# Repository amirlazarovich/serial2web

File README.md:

# Serial to web
Sample code for AVR serial, web server and a web socket

Thanks to [Tomer Weller](https://github.com/tomerweller/serial-to-socketio)!

### Install
```javascript
sudo npm install
```

### Usage
```javascript
node app [options]

options:
-h,--help			 print usage
-p, --port			 set serial port [default: tty.usb*]
-b, --baudrate		 set baudrate [default: 9600]
-w, --webport		 set web port [default: 8000]
```

### Example
```javascript 
node app
```

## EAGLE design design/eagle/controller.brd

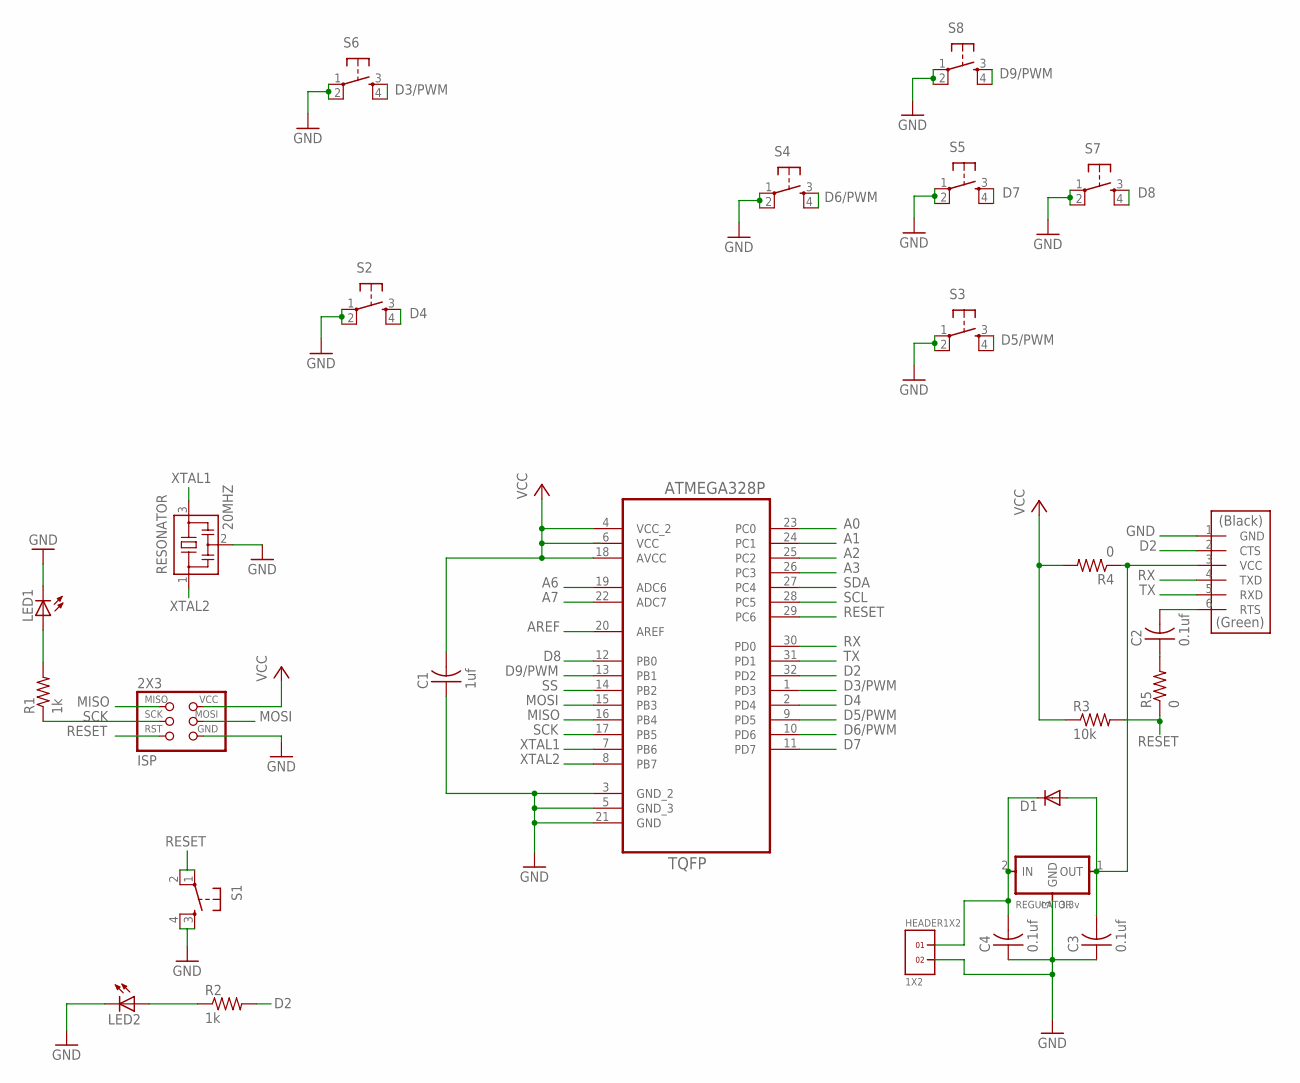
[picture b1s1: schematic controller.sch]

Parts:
2X3: ISP; 2X03SMD
C1: 1uf; C1206
C2, C3, C4: 0.1uf; C1206
D1: DIODESOD123; SOD123
FTDI: FTDI-SMD-HEADER; 1X06SMD
HEADER1X2: 1X2
LED1, LED2: LED_E; LED_1206
R1, R2: 1k; R1206
R3: 10k; R1206
R4, R5: 0; R1206
REGULATOR: 3.3v; SOT23
RESONATOR: 20MHZ; EFOBM
S1, S2, S3, S4, S5, S6, S7, S8: 6MM_SWITCH6MM_SWITCH; 6MM_SWITCH
U1: ATMEGA328P-AU; QFP80P900X900X120-32N

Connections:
A0: U1.23 (PC0)
A1: U1.24 (PC1)
A2: U1.25 (PC2)
A3: U1.26 (PC3)
A6: U1.19 (ADC6)
A7: U1.22 (ADC7)
AREF: U1.20 (AREF)
D2: FTDI.2 (CTS), R2.2, U1.32 (PD2)
D3/PWM: S6.3 (S), S6.4 (S1), U1.1 (PD3)
D4: S2.3 (S), S2.4 (S1), U1.2 (PD4)
D5/PWM: S3.3 (S), S3.4 (S1), U1.9 (PD5)
D6/PWM: S4.3 (S), S4.4 (S1), U1.10 (PD6)
D7: S5.3 (S), S5.4 (S1), U1.11 (PD7)
D8: S7.3 (S), S7.4 (S1), U1.12 (PB0)
D9/PWM: S8.3 (S), S8.4 (S1), U1.13 (PB1)
GND: 2X3.6 (GND), C1.1, C3.1, C4.1, FTDI.1 (GND), HEADER1X2.2, LED1.C, LED2.C, REGULATOR.3 (GND), RESONATOR.2, S1.3 (S), S1.4 (S1), S2.1, S2.2 (P1), S3.1, S3.2 (P1), S4.1, S4.2 (P1), S5.1, S5.2 (P1), S6.1, S6.2 (P1), S7.1, S7.2 (P1), S8.1, S8.2 (P1), U1.3 (GND_2), U1.5 (GND_3), U1.21 (GND)
MISO: 2X3.1 (MISO), U1.16 (PB4)
MOSI: 2X3.4 (MOSI), U1.15 (PB3)
unnamed: LED1.A, R1.2
unnamed: LED2.A, R2.1
unnamed: C2.1, R5.2
unnamed: C4.2, D1.CATHODE (C), HEADER1X2.1, REGULATOR.2 (IN)
unnamed: C3.2, D1.ANODE (A), FTDI.3 (VCC), R4.1, REGULATOR.1 (OUT)
unnamed: C2.2, FTDI.6 (RTS)
RESET: 2X3.5 (RST), R3.2, R5.1, S1.1, S1.2 (P1), U1.29 (PC6)
RX: FTDI.4 (TXD), U1.30 (PD0)
SCK: 2X3.3 (SCK), R1.1, U1.17 (PB5)
SCL: U1.28 (PC5)
SDA: U1.27 (PC4)
SS: U1.14 (PB2)
TX: FTDI.5 (RXD), U1.31 (PD1)
VCC: 2X3.2 (VCC), C1.2, R3.1, R4.2, U1.4 (VCC_2), U1.6 (VCC), U1.18 (AVCC)
XTAL1: RESONATOR.3, U1.7 (PB6)
XTAL2: RESONATOR.1, U1.8 (PB7)

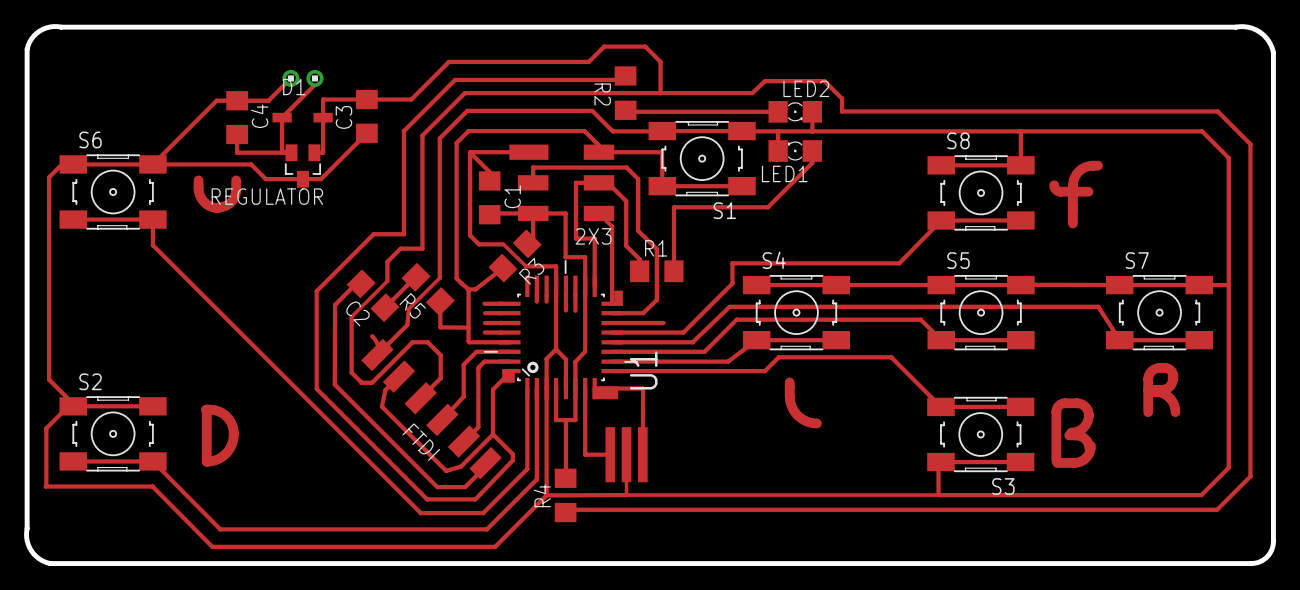
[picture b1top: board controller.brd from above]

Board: 2 copper layers, 103.4 x 44.5 mm, 26 parts (0 on the bottom side), 24 nets.

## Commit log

2014-11-19 readme
2014-11-19 added board
2014-11-19 cleanup
2014-11-19 few touchups
2014-11-19 minor changes
2014-11-20 minor change
2014-11-21 fucking workaround not needed
